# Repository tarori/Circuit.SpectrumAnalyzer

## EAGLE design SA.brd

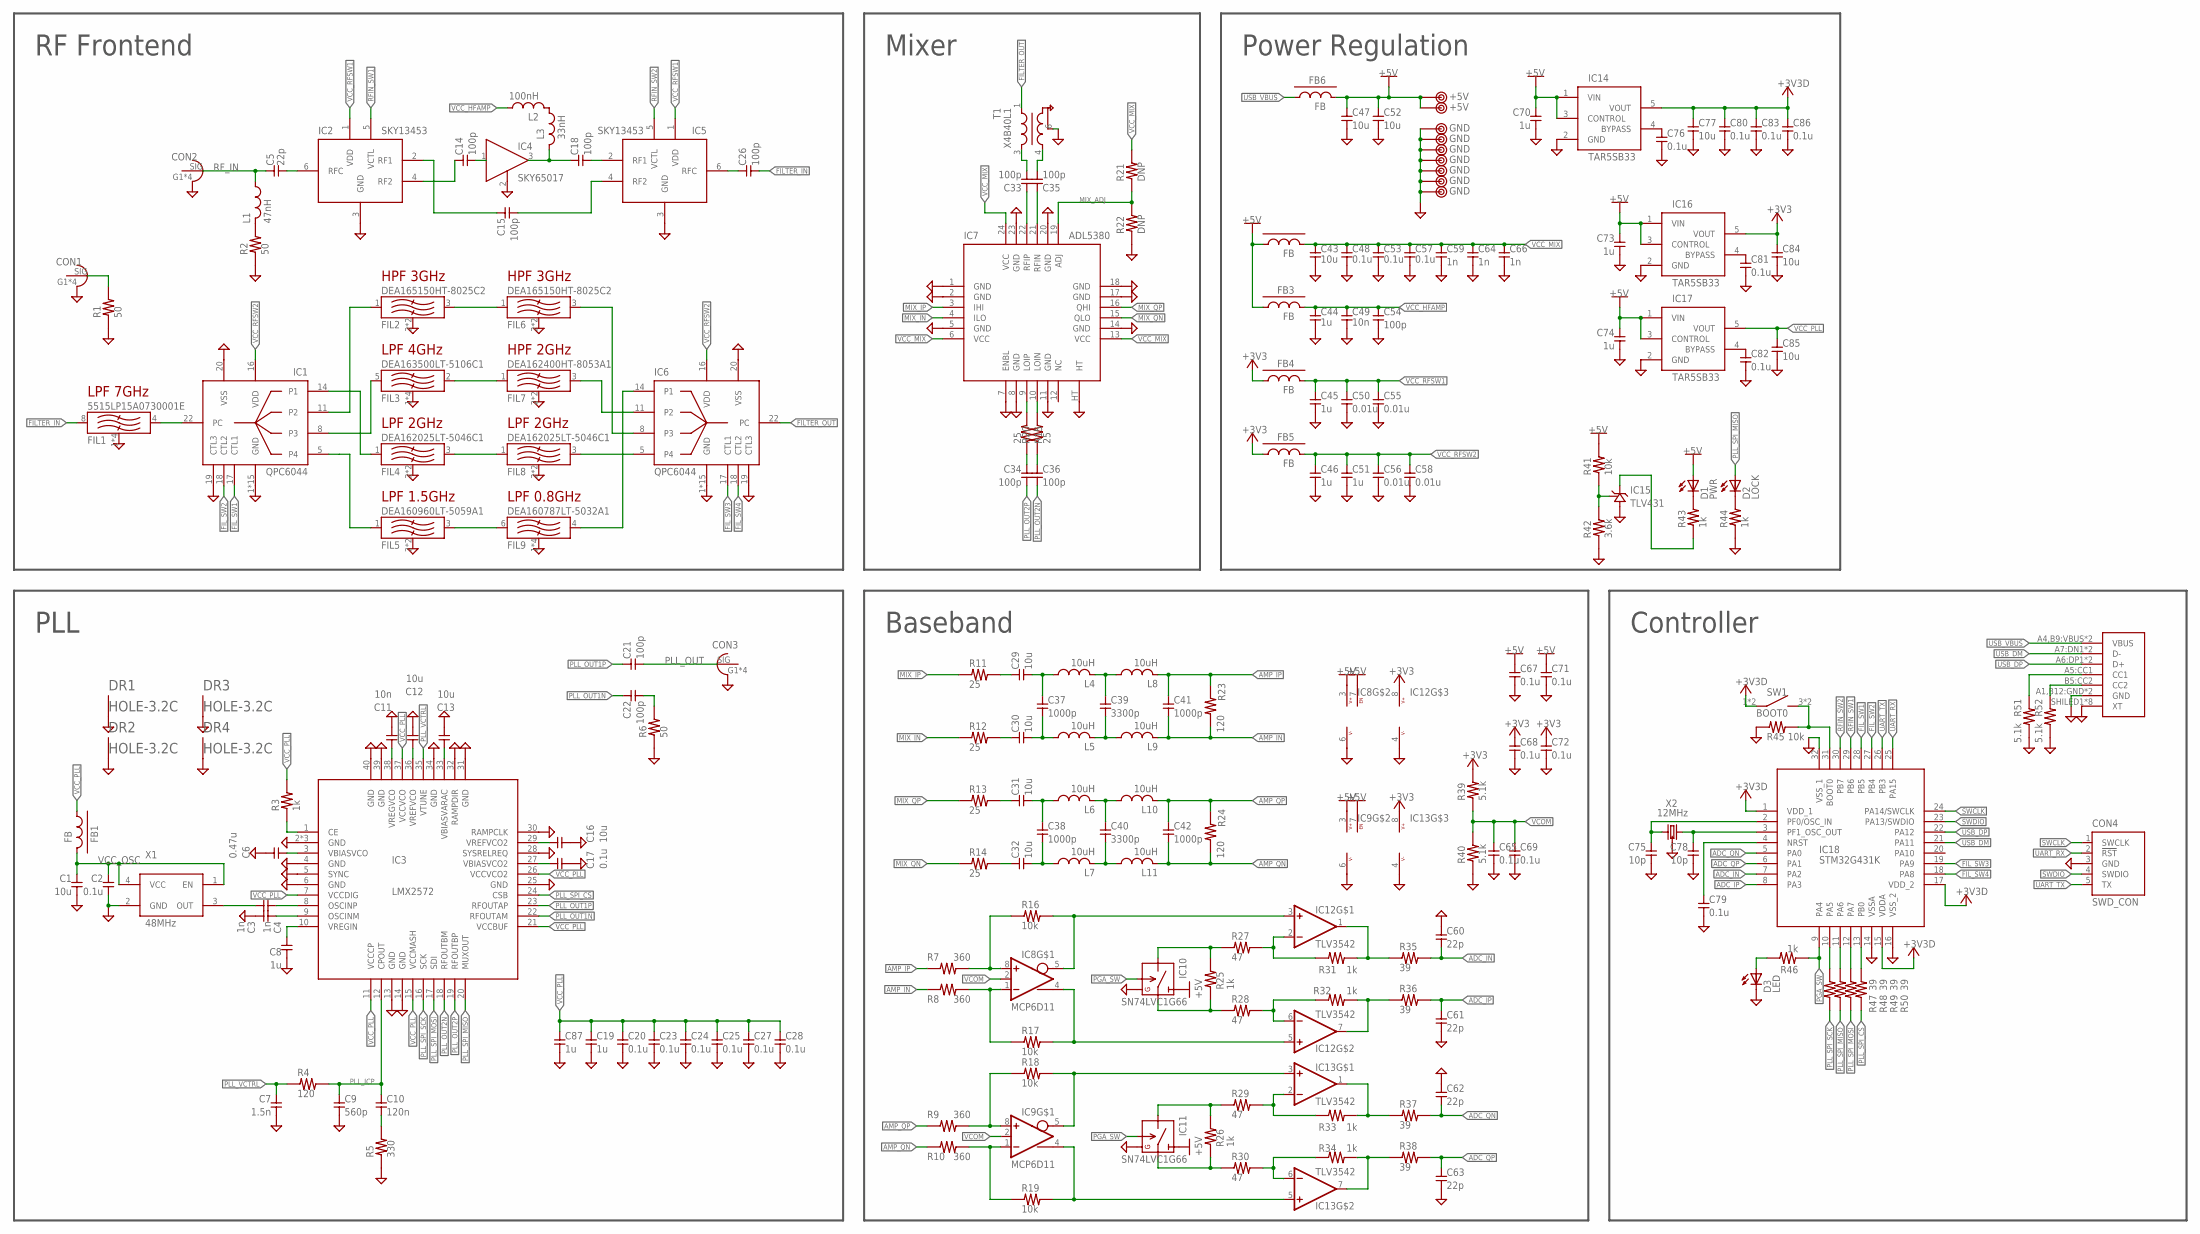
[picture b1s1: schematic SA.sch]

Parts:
C1, C43, C52, C77, C84, C85: 10u; 2012
C2, C17, C20, C23, C24, C25, C27, C28, C48, C53, C57, C65, C67, C68, C69, C71, C72, C76, C79, C80, C81, C82, C83, C86: 0.1u; 1608C
C3, C4, C59, C64, C66: 1n; 1005
C5: 22p; 1005RF
C6: 0.47u; 1608C
C7: 1.5n; 1608C
C8, C19, C44, C45, C46, C51, C70, C73, C74, C87: 1u; 1608C
C9: 560p; 1608C
C10: 120n; 1608C
C11, C49: 10n; 1608C
C12, C13, C16, C29, C30, C31, C32: 10u; 1608C
C14, C15, C18, C21, C22, C26, C33, C34, C35, C36: 100p; 1005RF
C37, C38, C41, C42: 1000p; 1608C
C39, C40: 3300p; 1608C
C47: 10u; 3216
C50, C55, C56, C58: 0.01u; 1608C
C54: 100p; 1005
C60, C61, C62, C63: 22p; 1608C
C75, C78: 10p; 1608C
CON1: DM_L; SMA-EDGE
CON2: RF_IN; SMA-EDGE
CON3: PLL_OUT; SMA-EDGE
CON4: SWD_CON
CON5: USB-C; 5077CR-16-SMC2-BK-TR
D1: PWR; D1608
D2: LOCK; D1608
D3: LED; D1608
DR1, DR2, DR3, DR4: HOLE-3.2C; HOLE_3.2_CON2
FB1, FB2, FB3, FB4, FB5: FB; 1608-FB
FB6: FB; 2012-R
FIL1: 5515LP15A0730001E; RF-FILTER-2012-JOHANSON
FIL2, FIL6: DEA165150HT-8025C2; RF-FILTER-1608-TDK
FIL3: DEA163500LT-5106C1; RF-FILTER-1608-TDK2
FIL4, FIL8: DEA162025LT-5046C1; RF-FILTER-1608-TDK
FIL5: DEA160960LT-5059A1; RF-FILTER-1608-TDK
FIL7: DEA162400HT-8053A1; RF-FILTER-1608-TDK
FIL9: DEA160787LT-5032A1; RF-FILTER-1608-TDK2
IC1, IC6: QPC6044; QFN24-QPC6044
IC2, IC5: SKY13453
IC3: LMX2572; QFN40-LMX
IC4: SKY65017; SOT89-RF
IC7: ADL5380; LFCSP24
IC8, IC9: MCP6D11; MSOP8
IC10, IC11: SN74LVC1G66; SOT23-5-2
IC12, IC13: TLV3542; SOP8-3
IC14, IC16, IC17: TAR5SB33; SOT23-5
IC15: TLV431; SC59
IC18: STM32G431K; TQFP32-08
L1: 47nH; 1005RF
L2: 100nH; 1608-L
L3: 33nH; 1005RF
L4, L5, L6, L7, L8, L9, L10, L11: 10uH; 2012-R
R1, R2, R6: 50; 1005RF
R3, R25, R26, R43, R44, R46: 1k; 1608
R4, R23, R24: 120; 1608
R5: 330; 1608
R7, R8, R9, R10: 360; 1608
R11, R12, R13, R14: 25; 1608
R15, R20: 25; 1005RF
R16, R18, R41, R45: 10k; 1608
R17, R19: 10k; 1608-3
R21, R22: DNP; 1608
R27, R28, R29, R30: 47; 1608-3
R31, R32, R33, R34: 1k; 1608-3
R35, R36, R37, R38, R47, R48, R49, R50: 39; 1608
R39, R40, R51, R52: 5.1k; 1608
R42: 3.6k; 1608
SW1: BOOT0; SKRPACE010
T1: X4B40L1
TP1, TP4: +5V; TESTPIN
TP2, TP3, TP5, TP6, TP7, TP8, TP9: GND; TESTPIN
X1: 48MHz; KC3225
X2: 12MHz; KC3225-CRYSTAL

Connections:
+3V3: C68.1, C72.1, C84.1, FB4.1, FB5.1, IC12.8 (V+), IC13.8 (V+), IC16.5 (VOUT), R39.2
+3V3D: C77.1, C80.1, C83.1, C86.1, IC14.5 (VOUT), IC18.1 (VDD_1), IC18.15 (VDDA), IC18.17 (VDD_2), SW1.1, SW1.2 (1)
+5V: C47.1, C52.1, C67.1, C70.1, C71.1, C73.1, C74.1, D1.A, FB2.1, FB3.1, FB6.2, IC8.3 (V+), IC8.7 (EN), IC9.3 (V+), IC9.7 (EN), IC10.5 (VCC), IC11.5 (VCC), IC14.1 (VIN), IC14.3 (CONTROL), IC16.1 (VIN), IC16.3 (CONTROL), IC17.1 (VIN), IC17.3 (CONTROL), R41.2, TP1.1, TP4.1
ADC_IN: C60.2, IC18.7 (PA2), R35.2
ADC_IP: C61.1, IC18.8 (PA3), R36.2
ADC_QN: C62.2, IC18.5 (PA0), R37.2
ADC_QP: C63.1, IC18.6 (PA1), R38.2
AMP_IN: C41.2, L9.2, R8.1, R23.1
AMP_IP: C41.1, L8.2, R7.1, R23.2
AMP_QN: C42.2, L11.2, R10.1, R24.1
AMP_QP: C42.1, L10.2, R9.1, R24.2
DUMMY_LOAD: CON1.SIG, R1.2
FILTER_IN: C26.2, FIL1.8 (IN)
FILTER_OUT: IC6.22 (PC), T1.1 (IN)
FIL_SW1: IC1.17 (CTL1), IC18.28 (PB5)
FIL_SW2: IC1.18 (CTL2), IC18.27 (PB4)
FIL_SW3: IC6.17 (CTL1), IC18.19 (PA9)
FIL_SW4: IC6.18 (CTL2), IC18.18 (PA8)
GND: C1.2, C2.2, C4.2, C6.2, C7.2, C8.2, C9.2, C11.2, C12.2, C13.2, C16.2, C17.2, C19.2, C20.2, C23.2, C24.2, C25.2, C27.2, C28.2, C43.2, C44.2, C45.2, C46.2, C47.2, C48.2, C49.2, C50.2, C51.2, C52.2, C53.2, C54.2, C55.2, C56.2, C57.2, C58.2, C59.2, C60.1, C61.2, C62.1, C63.2, C64.2, C65.2, C66.2, C67.2, C68.2, C69.2, C70.2, C71.2, C72.2, C73.2, C74.2, C75.2, C76.2, C77.2, C78.2, C79.2, C80.2, C81.2, C82.2, C83.2, C84.2, C85.2, C86.2, C87.2, CON1.G1 (GND), CON1.G2 (GND), CON1.G3 (GND), CON1.G4 (GND), CON2.G1 (GND), CON2.G2 (GND), CON2.G3 (GND), CON2.G4 (GND), CON3.G1 (GND), CON3.G2 (GND), CON3.G3 (GND), CON3.G4 (GND), CON4.3 (GND), CON5.A1,B12:GND (GND), CON5.B1,A12:GND (GND), CON5.SHILED1 (XT), CON5.SHILED2 (XT), CON5.SHILED3 (XT), CON5.SHILED4 (XT), CON5.SHILED5 (XT), CON5.SHILED6 (XT), CON5.SHILED7 (XT), CON5.SHILED8 (XT), D3.K, DR1.T, DR2.T, DR3.T, DR4.T, FIL1.1 (GND), FIL1.3 (GND), FIL1.5 (GND), FIL1.7 (GND), FIL2.2 (GND), FIL2.4 (GND), FIL3.1 (GND), FIL3.3 (GND), FIL3.4 (GND), FIL3.6 (GND), FIL4.2 (GND), FIL4.4 (GND), FIL5.2 (GND), FIL5.4 (GND), FIL6.2 (GND), FIL6.4 (GND), FIL7.2 (GND), FIL7.4 (GND), FIL8.2 (GND), FIL8.4 (GND), FIL9.1 (GND), FIL9.2 (GND), FIL9.3 (GND), FIL9.5 (GND), IC1.1 (GND), IC1.2 (GND), IC1.3 (GND), IC1.4 (GND), IC1.6 (GND), IC1.7 (GND), IC1.9 (GND), IC1.10 (GND), IC1.12 (GND), IC1.13 (GND), IC1.15 (GND), IC1.19 (CTL3), IC1.20 (VSS), IC1.21 (GND), IC1.23 (GND), IC1.24 (GND), IC1.HT (GND), IC2.3 (GND), IC3.2 (GND), IC3.4 (GND), IC3.5 (SYNC), IC3.6 (GND), IC3.13 (GND), IC3.14 (GND), IC3.25 (GND), IC3.28 (SYSRELREQ), IC3.30 (RAMPCLK), IC3.31 (GND), IC3.32 (RAMPDIR), IC3.34 (GND), IC3.39 (GND), IC3.40 (GND), IC3.HT (GND), IC3.HT2 (GND), IC4.2 (GND), IC5.3 (GND), IC6.1 (GND), IC6.2 (GND), IC6.3 (GND), IC6.4 (GND), IC6.6 (GND), IC6.7 (GND), IC6.9 (GND), IC6.10 (GND), IC6.12 (GND), IC6.13 (GND), IC6.15 (GND), IC6.19 (CTL3), IC6.20 (VSS), IC6.21 (GND), IC6.23 (GND), IC6.24 (GND), IC6.HT (GND), IC7.1 (GND), IC7.2 (GND), IC7.5 (GND), IC7.7 (ENBL), IC7.8 (GND), IC7.11 (GND), IC7.14 (GND), IC7.17 (GND), IC7.18 (GND), IC7.20 (GND), IC7.23 (GND), IC7.HT, IC8.6 (V-), IC9.6 (V-), IC10.3 (GND), IC11.3 (GND), IC12.4 (V-), IC13.4 (V-), IC14.2 (GND), IC15.3 (GND), IC16.2 (GND), IC17.2 (GND), IC18.14 (VSSA), IC18.16 (VSS_2), IC18.32 (VSS_1), R1.1, R2.1, R5.1, R6.1, R22.1, R40.1, R42.1, R44.1, R45.1, R51.1, R52.1, T1.6 (GND), TP2.1, TP3.1, TP5.1, TP6.1, TP7.1, TP8.1, TP9.1, X1.2 (GND), X2.2 (GND), X2.4 (GND)
MIX_ADJ: IC7.19 (ADJ), R21.1, R22.2
MIX_IN: IC7.4 (ILO), R12.1
MIX_IP: IC7.3 (IHI), R11.1
MIX_QN: IC7.15 (QLO), R14.1
MIX_QP: IC7.16 (QHI), R13.1
unnamed: C14.1, IC2.4 (RF2)
unnamed: C10.2, R5.2
unnamed: C39.1, L4.2, L8.1
unnamed: C35.2, T1.4 (OUTN)
unnamed: C13.1, IC3.33 (VBIASVARAC)
unnamed: C39.2, L5.2, L9.1
unnamed: C31.2, C38.1, L6.1
unnamed: C33.1, IC7.22 (RFIP)
unnamed: C32.2, C38.2, L7.1
unnamed: C40.1, L6.2, L10.1
unnamed: C40.2, L7.2, L11.1
unnamed: C16.1, IC3.29 (VREFVCO2)
unnamed: C82.1, IC17.4 (BYPASS)
unnamed: L2.2, L3.1
unnamed: IC15.1 (REF), R41.1, R42.2
unnamed: IC15.2 (OUT), R43.1
unnamed: C34.1, R15.1
unnamed: C36.1, R20.1
unnamed: IC18.10 (PA5), R47.1
unnamed: C35.1, IC7.21 (RFIN)
unnamed: C3.2, X1.3 (OUT)
unnamed: C81.1, IC16.4 (BYPASS)
unnamed: L1.2, R2.2
unnamed: IC18.11 (PA6), R48.1
unnamed: IC18.12 (PA7), R49.1
unnamed: C22.2, R6.2
unnamed: IC18.13 (PB0), R50.1
unnamed: D3.A, R46.2
unnamed: CON5.B5:CC2 (CC2), R52.2
unnamed: CON5.A5:CC1 (CC1), R51.2
unnamed: C29.2, C37.1, L4.1
unnamed: C30.2, C37.2, L5.1
unnamed: IC7.9 (LOIP), R15.2
unnamed: IC7.10 (LOIN), R20.2
unnamed: D1.K, R43.2
unnamed: D2.K, R44.2
unnamed: FIL1.4 (OUT), IC1.22 (PC)
unnamed: C15.1, IC2.2 (RF1)
unnamed: C15.2, IC5.4 (RF2)
unnamed: C26.1, IC5.6 (RFC)
unnamed: C5.2, IC2.6 (RFC)
unnamed: C14.2, IC4.1 (IN)
unnamed: C18.1, IC4.3 (OUT), L3.2
unnamed: FIL5.1 (IN), IC1.5 (P4)
unnamed: FIL4.1 (IN), IC1.14 (P1)
unnamed: FIL2.1 (IN), IC1.11 (P2)
unnamed: FIL4.3 (OUT), FIL8.1 (IN)
unnamed: FIL6.3 (OUT), IC6.8 (P3)
unnamed: FIL5.3 (OUT), FIL9.6 (IN)
unnamed: FIL3.2 (OUT), FIL7.1 (IN)
unnamed: FIL7.3 (OUT), IC6.11 (P2)
unnamed: FIL9.4 (OUT), IC6.14 (P1)
unnamed: FIL8.3 (OUT), IC6.5 (P4)
unnamed: C4.1, IC3.9 (OSCINM)
unnamed: C33.2, T1.3 (OUTP)
unnamed: C18.2, IC5.2 (RF1)
unnamed: C29.1, R11.2
unnamed: C30.1, R12.2
unnamed: C31.1, R13.2
unnamed: C32.1, R14.2
unnamed: IC8.8 (+IN), R7.2, R16.1
unnamed: IC8.1 (-IN), R8.2, R17.1
unnamed: IC8.5 (-OUT), IC12.3 (+IN), R16.2
unnamed: IC13.2 (-IN), R29.2, R33.2
unnamed: IC9.8 (+IN), R9.2, R18.1
unnamed: IC9.1 (-IN), R10.2, R19.1
unnamed: IC12.6 (-IN), R28.2, R32.2
unnamed: IC9.5 (-OUT), IC13.3 (+IN), R18.2
unnamed: C76.1, IC14.4 (BYPASS)
unnamed: C75.1, IC18.2 (PF0/OSC_IN), X2.3 (2)
unnamed: C78.1, IC18.3 (PF1_OSC_OUT), X2.1
unnamed: FIL2.3 (OUT), FIL6.1 (IN)
unnamed: IC12.2 (-IN), R27.2, R31.2
unnamed: IC8.4 (+OUT), IC12.5 (+IN), R17.2
unnamed: IC12.1 (OUT), R31.1, R35.1
unnamed: IC9.4 (+OUT), IC13.5 (+IN), R19.2
unnamed: IC13.7 (OUT), R34.1, R38.1
unnamed: IC12.7 (OUT), R32.1, R36.1
unnamed: IC13.6 (-IN), R30.2, R34.2
unnamed: IC13.1 (OUT), R33.1, R37.1
unnamed: IC10.2 (B), R25.1, R28.1
unnamed: IC10.1 (A), R25.2, R27.1
unnamed: IC11.2 (B), R26.1, R30.1
unnamed: IC11.1 (A), R26.2, R29.1
unnamed: FIL3.5 (IN), IC1.8 (P3)
unnamed: C3.1, IC3.8 (OSCINP)
unnamed: C12.1, IC3.36 (VREFVCO)
unnamed: C11.1, IC3.38 (VREGVCO)
unnamed: C6.1, IC3.3 (VBIASVCO)
unnamed: C8.1, IC3.10 (VREGIN)
unnamed: C17.1, IC3.27 (VBIASVCO2)
PGA_SW: IC10.4 (S), IC11.4 (S), IC18.9 (PA4), R46.1
PLL_EN: IC3.1 (CE), R3.1
PLL_ICP: C9.1, C10.1, IC3.12 (CPOUT), R4.2
PLL_OUT: C21.2, CON3.SIG
PLL_OUT1N: C22.1, IC3.22 (RFOUTAM)
PLL_OUT1P: C21.1, IC3.23 (RFOUTAP)
PLL_OUT2N: C36.2, IC3.18 (RFOUTBM)
PLL_OUT2P: C34.2, IC3.19 (RFOUTBP)
PLL_SPI_CS: IC3.24 (CSB), R50.2
PLL_SPI_MISO: D2.A, IC3.20 (MUXOUT), R48.2
PLL_SPI_MOSI: IC3.17 (SDI), R49.2
PLL_SPI_SCK: IC3.16 (SCK), R47.2
PLL_VCTRL: C7.1, IC3.35 (VTUNE), R4.1
RFIN_SW1: IC2.5 (VCTL), IC18.29 (PB6)
RFIN_SW2: IC5.5 (VCTL), IC18.30 (PB7)
RF_IN: C5.1, CON2.SIG, L1.1
ST_BOOT0: IC18.31 (BOOT0), R45.2, SW1.3 (2), SW1.4 (2)
ST_NRST: C79.1, IC18.4 (NRST)
SWCLK: CON4.1 (SWCLK), IC18.24 (PA14/SWCLK)
SWDIO: CON4.4 (SWDIO), IC18.23 (PA13/SWDIO)
UART_RX: CON4.2 (!RST), IC18.25 (PA15)
UART_TX: CON4.5 (TX), IC18.26 (PB3)
USB_DM: CON5.A7:DN1 (D-), CON5.B7:DN2 (D-), IC18.21 (PA11)
USB_DP: CON5.A6:DP1 (D+), CON5.B6:DP2 (D+), IC18.22 (PA12)
USB_VBUS: CON5.A4,B9:VBUS (VBUS), CON5.B4,A9:VBUS (VBUS), FB6.1
VCC_HFAMP: C44.1, C49.1, C54.1, FB3.2, L2.1
VCC_MIX: C43.1, C48.1, C53.1, C57.1, C59.1, C64.1, C66.1, FB2.2, IC7.6 (VCC), IC7.13 (VCC), IC7.24 (VCC), R21.2
VCC_OSC: C1.1, C2.1, FB1.2, X1.1 (EN), X1.4 (VCC)
VCC_PLL: C19.1, C20.1, C23.1, C24.1, C25.1, C27.1, C28.1, C85.1, C87.1, FB1.1, IC3.7 (VCCDIG), IC3.11 (VCCCP), IC3.15 (VCCMASH), IC3.21 (VCCBUF), IC3.26 (VCCVCO2), IC3.37 (VCCVCO), IC17.5 (VOUT), R3.2
VCC_RFSW1: C45.1, C50.1, C55.1, FB4.2, IC2.1 (VDD), IC5.1 (VDD)
VCC_RFSW2: C46.1, C51.1, C56.1, C58.1, FB5.2, IC1.16 (VDD), IC6.16 (VDD)
VCOM: C65.1, C69.1, IC8.2 (CM), IC9.2 (CM), R39.1, R40.2

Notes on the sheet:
LPF 7GHz
HPF 3GHz
LPF 4GHz
LPF 2GHz
LPF 1.5GHz
LPF 0.8GHz
HPF 2GHz
RF Frontend
Mixer
PLL
Baseband
Power Regulation
Controller

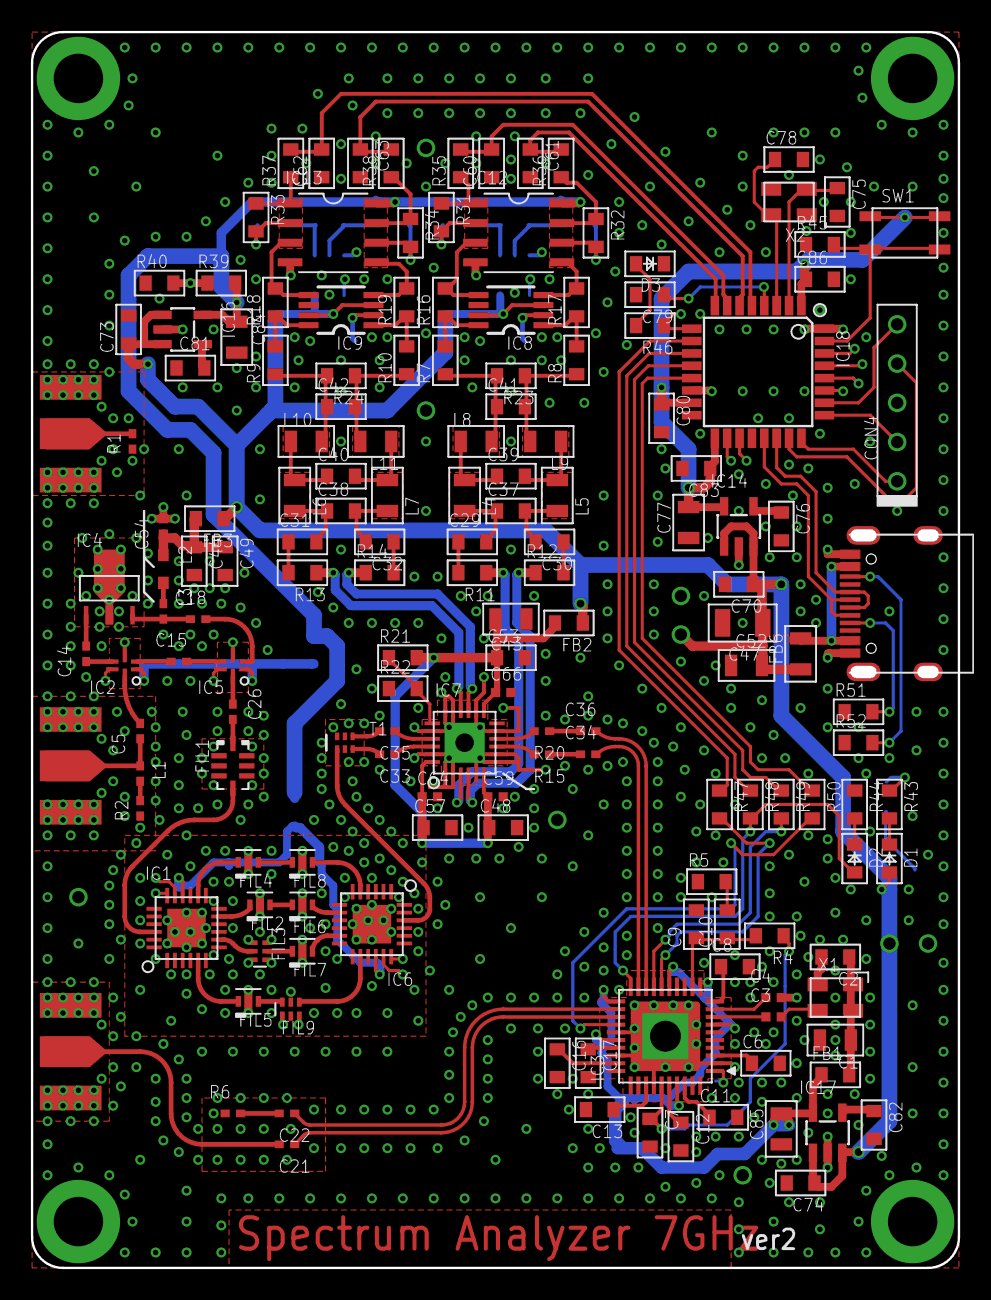
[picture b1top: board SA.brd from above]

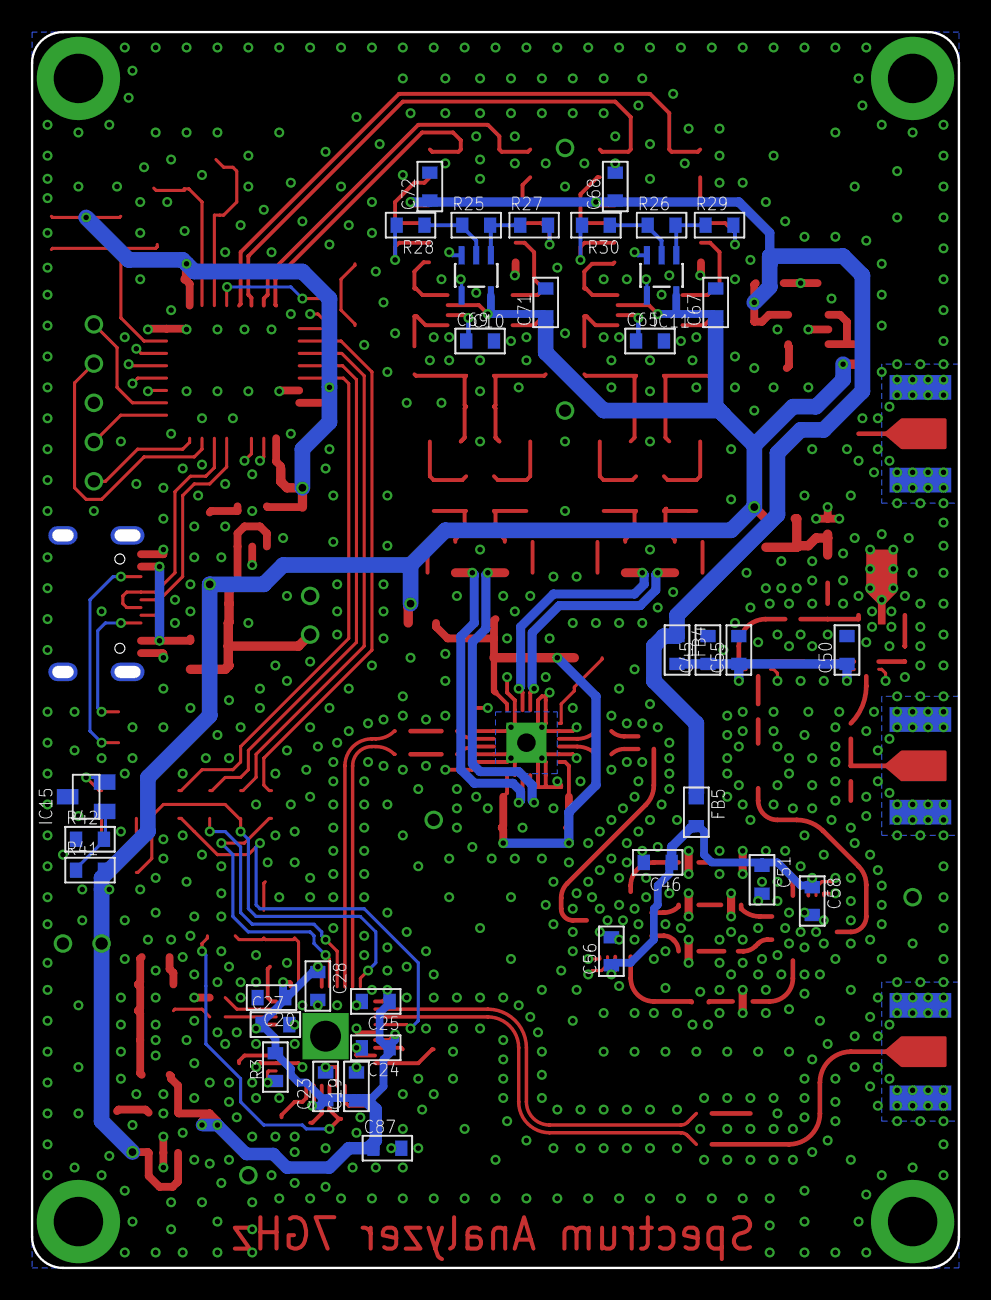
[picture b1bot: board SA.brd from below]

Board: 4 copper layers, 60.0 x 80.0 mm, 208 parts (35 on the bottom side), 147 nets.

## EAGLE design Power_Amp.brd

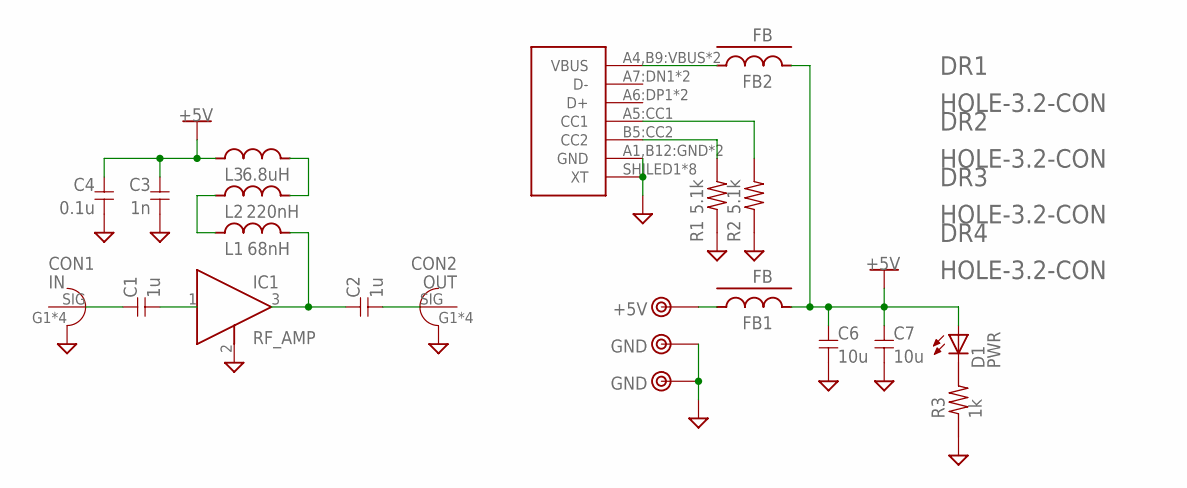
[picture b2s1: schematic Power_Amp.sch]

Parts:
C1, C2: 1u; 1608-3
C3: 1n; 1005
C4: 0.1u; 1608C
C6, C7: 10u; 2012
CON1: IN; SMA-EDGE3
CON2: OUT; SMA-EDGE3
CON3: USB-C; 5077CR-16-SMC2-BK-TR
D1: PWR; D1608
DR1, DR2, DR3, DR4: HOLE-3.2-CON; HOLE_3.2_CON
FB1, FB2: FB; 1608-FB
IC1: RF_AMP; SOT89
L1: 68nH; 1005
L2: 220nH; 1608
L3: 6.8uH; 1608
R1, R2: 5.1k; 1608
R3: 1k; 1608
TP1: +5V; TESTPIN
TP2, TP3: GND; TESTPIN

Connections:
+5V: C3.1, C4.1, C6.1, C7.1, D1.A, FB1.2, FB2.2, L3.1
GND: C3.2, C4.2, C6.2, C7.2, CON1.G1 (GND), CON1.G2 (GND), CON1.G3 (GND), CON1.G4 (GND), CON2.G1 (GND), CON2.G2 (GND), CON2.G3 (GND), CON2.G4 (GND), CON3.A1,B12:GND (GND), CON3.B1,A12:GND (GND), CON3.SHILED1 (XT), CON3.SHILED2 (XT), CON3.SHILED3 (XT), CON3.SHILED4 (XT), CON3.SHILED5 (XT), CON3.SHILED6 (XT), CON3.SHILED7 (XT), CON3.SHILED8 (XT), IC1.2 (GND), R1.1, R2.1, R3.1, TP2.1, TP3.1
unnamed: C1.2, IC1.1 (IN)
unnamed: C1.1, CON1.SIG
unnamed: C2.1, IC1.3 (OUT), L1.2
unnamed: L1.1, L2.1
unnamed: L2.2, L3.2
unnamed: C2.2, CON2.SIG
unnamed: FB1.1, TP1.1
unnamed: D1.K, R3.2
unnamed: CON3.B5:CC2 (CC2), R1.2
unnamed: CON3.A5:CC1 (CC1), R2.2
unnamed: CON3.A4,B9:VBUS (VBUS), CON3.B4,A9:VBUS (VBUS), FB2.1

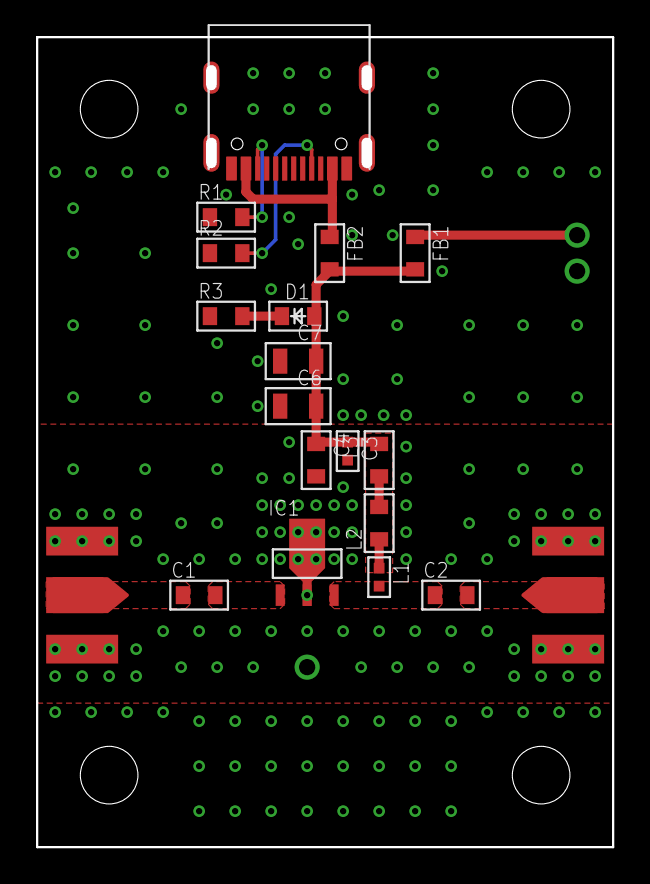
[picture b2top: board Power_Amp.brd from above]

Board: 2 copper layers, 32.0 x 45.0 mm, 26 parts (0 on the bottom side), 13 nets.

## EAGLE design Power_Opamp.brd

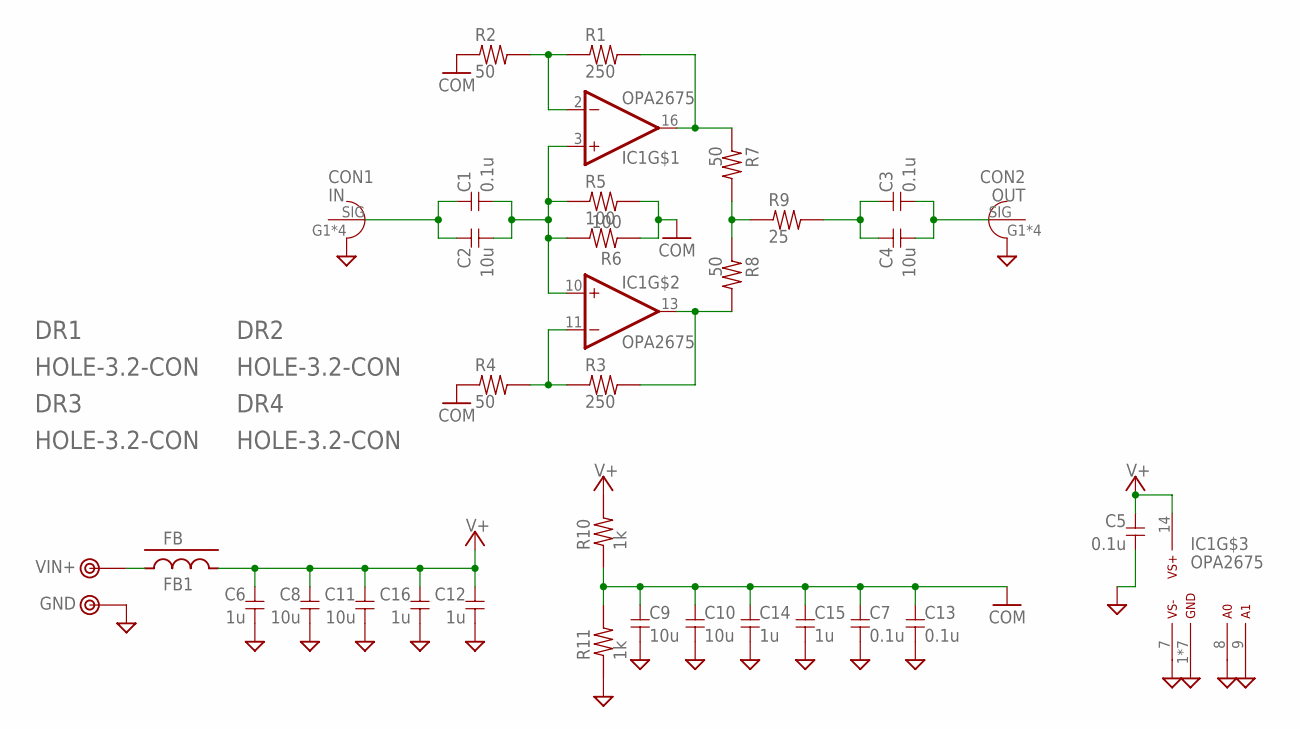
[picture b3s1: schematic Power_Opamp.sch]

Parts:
C1, C3: 0.1u; 1608C
C2, C4, C10, C11: 10u; 2012
C5, C7, C13: 0.1u; 1005
C6, C12, C14, C15, C16: 1u; 1608C
C8, C9: 10u; 3216
CON1: IN; SMA-EDGE
CON2: OUT; SMA-EDGE
DR1, DR2, DR3, DR4: HOLE-3.2-CON; HOLE_3.2_CON
FB1: FB; 2012-J
IC1: OPA2675; VQFN16
R1, R3: 250; 1608-3
R2, R4: 50; 1608-3
R5, R6: 100; 1608-3
R7, R8: 50; 1608
R9: 25; 1608
R10, R11: 1k; 1608
TP1: VIN+; TESTPIN-BIG
TP2: GND; TESTPIN-BIG

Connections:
AMP_IN: C1.2, C2.2, IC1.3 (+IN), IC1.10 (+IN), R5.1, R6.2
AMP_OUT: C3.1, C4.1, R9.2
COM: C7.1, C9.1, C10.1, C13.1, C14.1, C15.1, R2.1, R4.1, R5.2, R6.1, R10.1, R11.2
GND: C5.2, C6.2, C7.2, C8.2, C9.2, C10.2, C11.2, C12.2, C13.2, C14.2, C15.2, C16.2, CON1.G1 (GND), CON1.G2 (GND), CON1.G3 (GND), CON1.G4 (GND), CON2.G1 (GND), CON2.G2 (GND), CON2.G3 (GND), CON2.G4 (GND), IC1.1 (GND), IC1.4 (GND), IC1.5 (GND), IC1.6 (GND), IC1.7 (VS-), IC1.8 (A0), IC1.9 (A1), IC1.12 (GND), IC1.15 (GND), IC1.HT (GND), R11.1, TP2.1
unnamed: IC1.11 (-IN), R3.1, R4.2
unnamed: IC1.2 (-IN), R1.1, R2.2
unnamed: IC1.13 (OUT), R3.2, R8.2
unnamed: IC1.16 (OUT), R1.2, R7.1
unnamed: C1.1, C2.1, CON1.SIG
unnamed: C3.2, C4.2, CON2.SIG
unnamed: R7.2, R8.1, R9.1
unnamed: FB1.2, TP1.1
V+: C5.1, C6.1, C8.1, C11.1, C12.1, C16.1, FB1.1, IC1.14 (VS+), R10.2

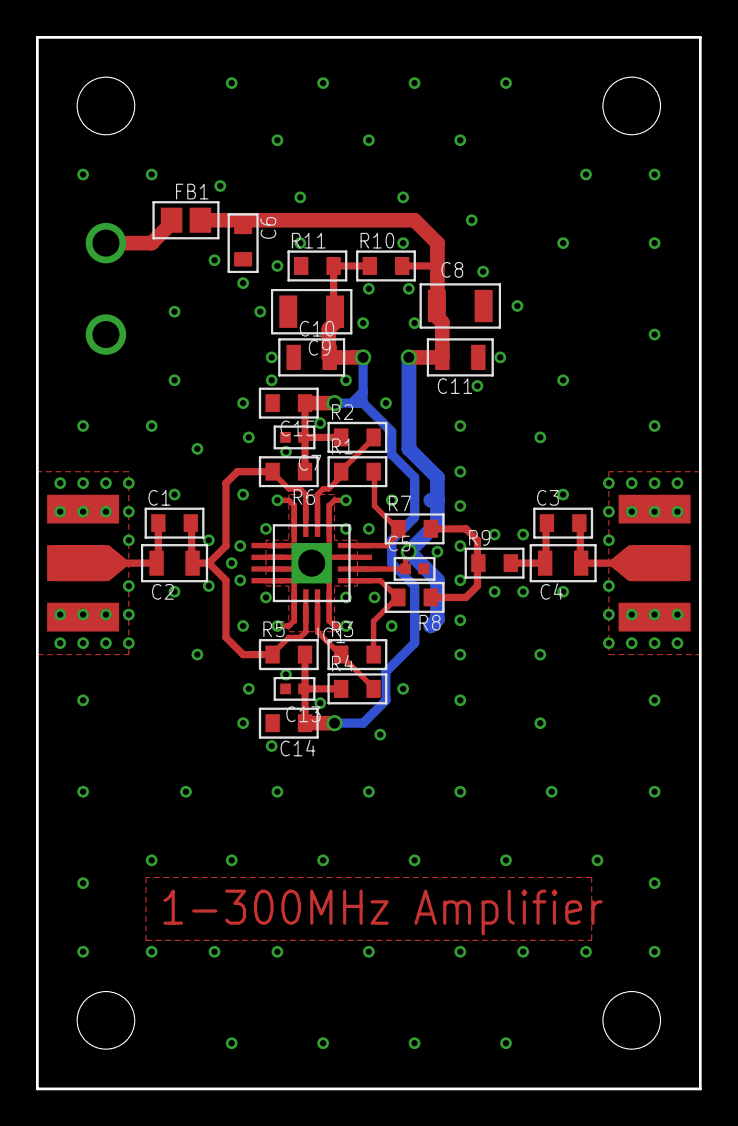
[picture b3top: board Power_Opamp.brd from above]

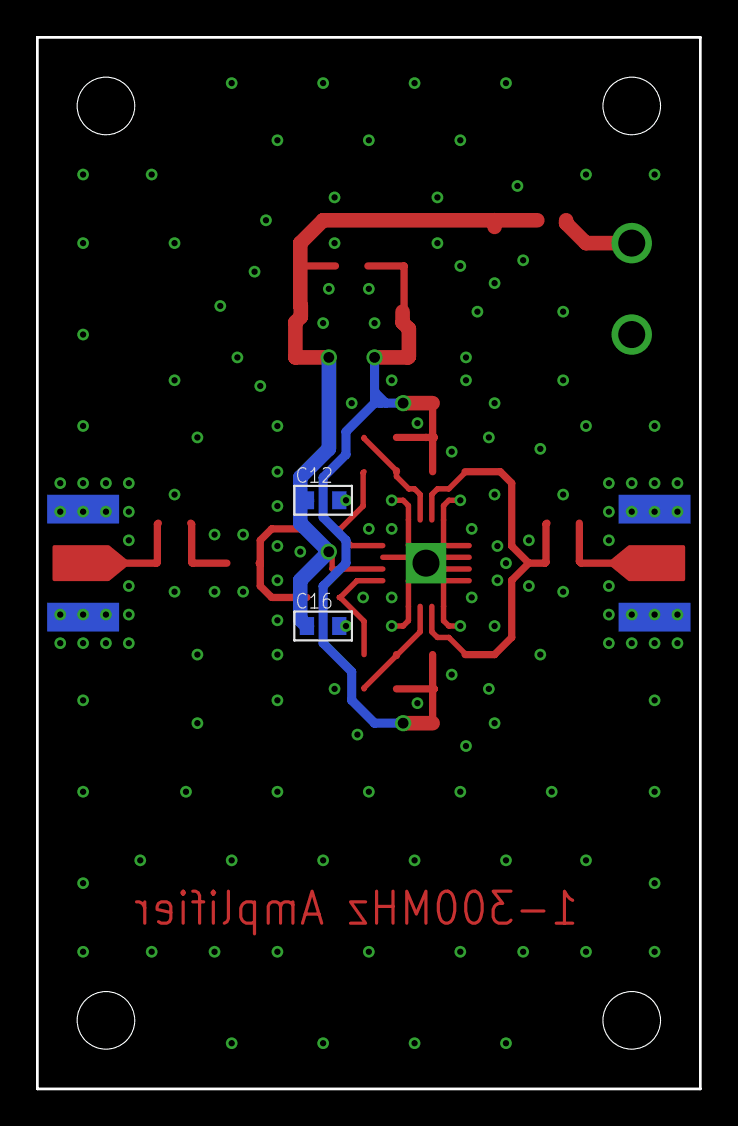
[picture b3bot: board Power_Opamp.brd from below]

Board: 2 copper layers, 36.8 x 58.4 mm, 37 parts (2 on the bottom side), 13 nets.

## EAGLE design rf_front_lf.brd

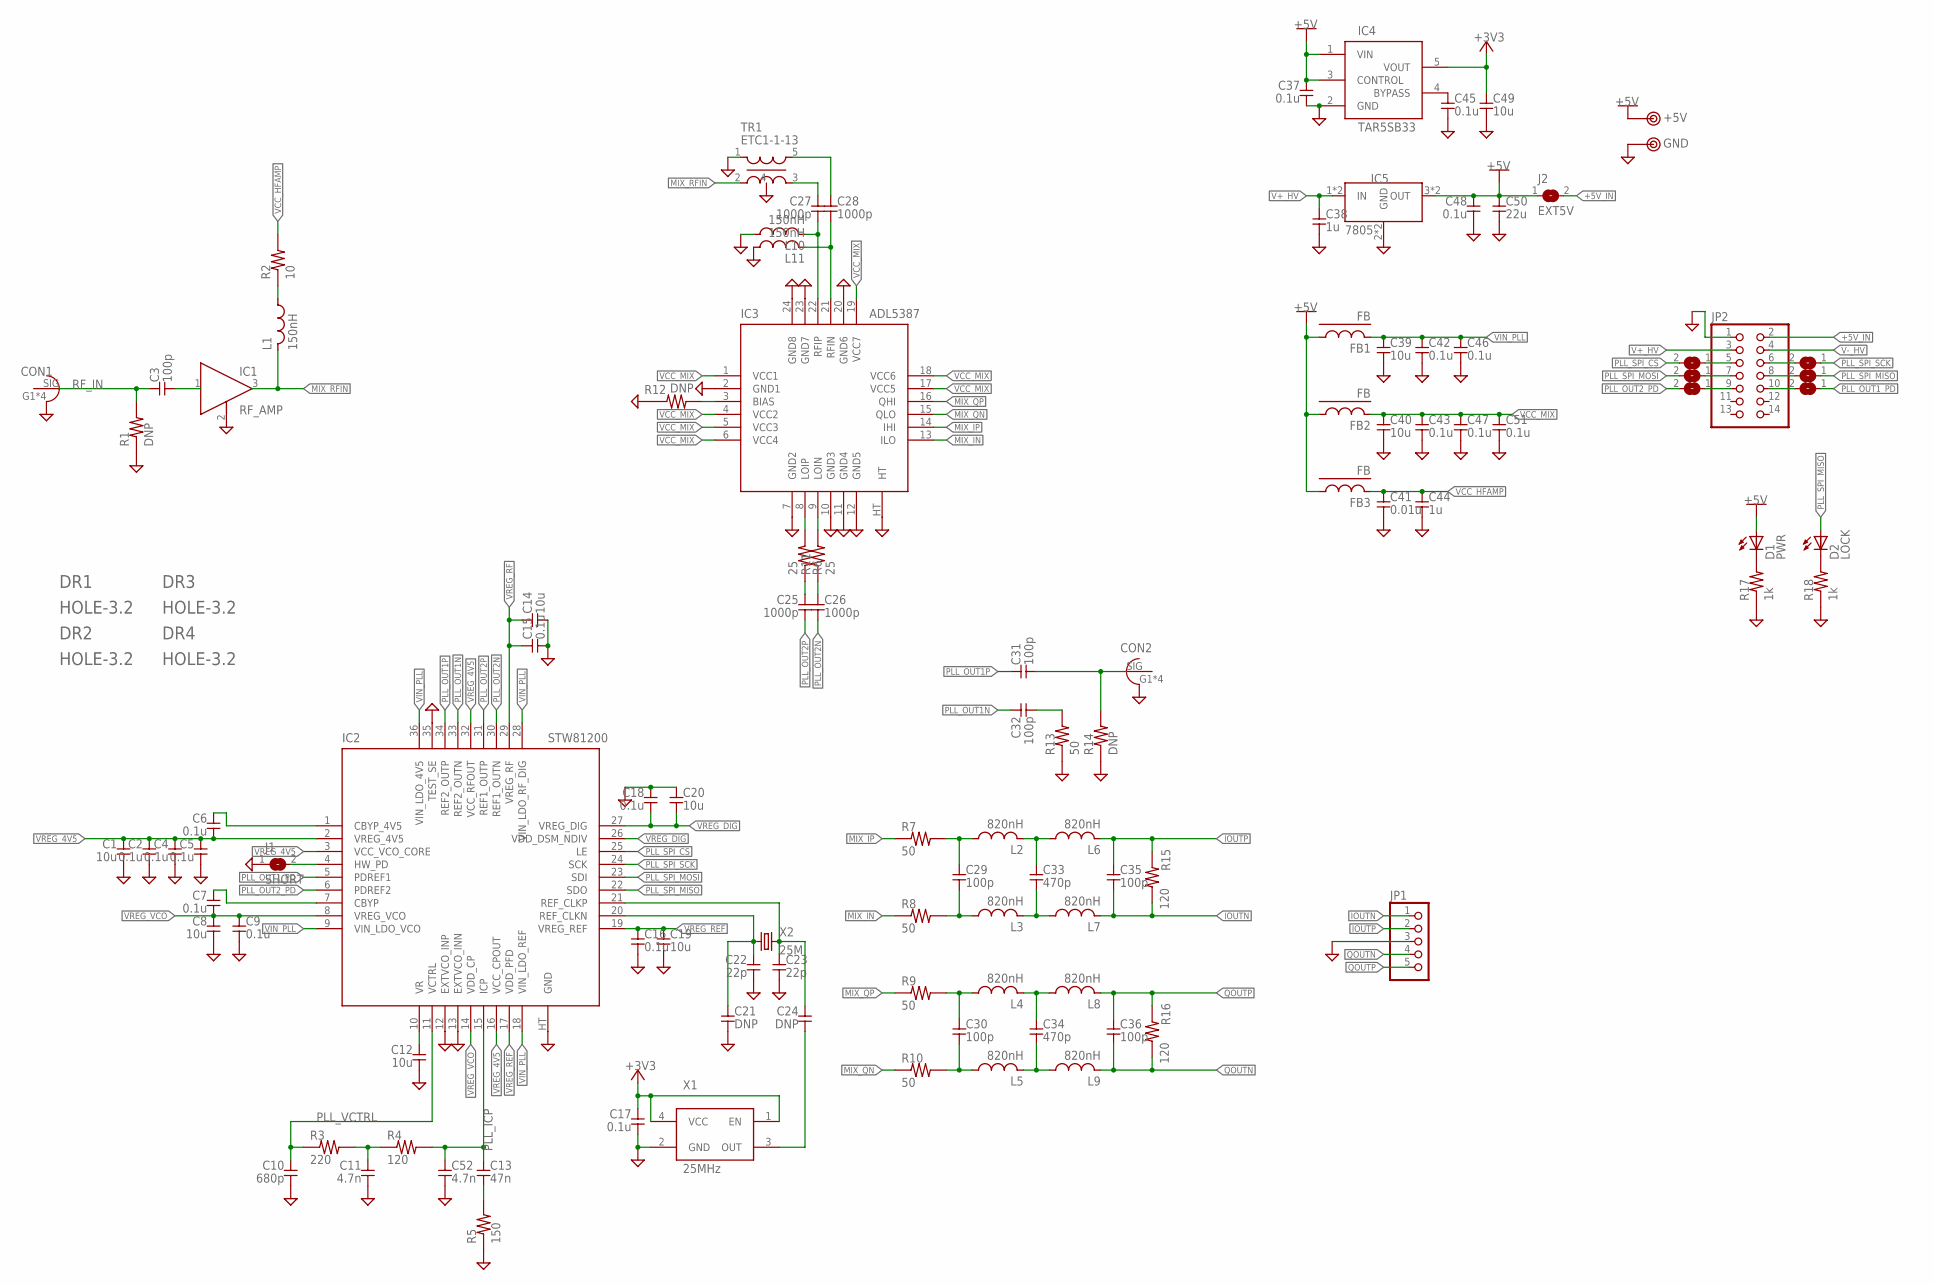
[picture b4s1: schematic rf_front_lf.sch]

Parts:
C1, C8, C12, C14, C19, C20, C49: 10u; 1608
C2, C4, C5, C6, C7, C9, C15, C16, C17, C18, C37, C42, C43, C45, C46, C47, C48, C51: 0.1u; 1608
C3, C29, C30, C31, C32, C35, C36: 100p; 1608
C10: 680p; 1608
C11, C52: 4.7n; 1608
C13: 47n; 1608
C21, C24: DNP; 1608
C22, C23: 22p; 1608
C25, C26, C27, C28: 1000p; 1608
C33, C34: 470p; 1608
C38, C44: 1u; 1608
C39, C40: 10u; 2012
C41: 0.01u; 1608
C50: 22u; 3225
CON1: RF_IN; SMA-EDGE
CON2: PLL_OUT; SMA-EDGE
D1: PWR; D1608
D2: LOCK; D1608
DR1, DR2, DR3, DR4: HOLE-3.2; HOLE_3.2
FB1, FB2, FB3: FB; 1608-J
IC1: RF_AMP; SOT89
IC2: STW81200; VFQFPN36
IC3: ADL5387; LFCSP24
IC4: TAR5SB33; SOT23-5
IC5: 7805; TO220-SOP-DUAL
J1: SHORT; 1608-J
J2: EXT5V; 1608-J
J3: CS; 1608-J
J4: MOSI; 1608-J
J5: PD2; 1608-J
J6: SCK; 1608-J
J7: MISO; 1608-J
J8: PD1; 1608-J
JP1: PINHD-1X5; 1X05
JP2: PINHD-2X7; 2X07
L1, L10, L11: 150nH; 1608
L2, L3, L4, L5, L6, L7, L8, L9: 820nH; 1608
R1, R12, R14: DNP; 1608
R2: 10; 1608
R3: 220; 1608
R4, R15, R16: 120; 1608
R5: 150; 1608
R6, R11: 25; 1608
R7, R8, R9, R10, R13: 50; 1608
R17, R18: 1k; 1608
TP1: +5V; TESTPIN
TP2: GND; TESTPIN
TR1: ETC1-1-13
X1: 25MHz; KC3225
X2: 25M; HC49/S

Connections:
+3V3: C17.1, C49.1, IC4.5 (VOUT), X1.1 (EN), X1.4 (VCC)
+5V: C37.1, C48.1, C50.1, D1.A, FB1.1, FB2.1, FB3.1, IC4.1 (VIN), IC4.3 (CONTROL), IC5.3 (OUT), IC5.6 (OUT), J2.1, TP1.1
+5V_IN: J2.2, JP2.2
GND: C1.2, C2.2, C4.2, C5.2, C8.2, C9.2, C10.2, C11.2, C12.2, C14.2, C15.2, C16.2, C17.2, C18.1, C19.2, C20.1, C21.2, C22.2, C23.2, C37.2, C38.2, C39.2, C40.2, C41.2, C42.2, C43.2, C44.2, C45.2, C46.2, C47.2, C48.2, C49.2, C50.2, C51.2, C52.2, CON1.G1 (GND), CON1.G2 (GND), CON1.G3 (GND), CON1.G4 (GND), CON2.G1 (GND), CON2.G2 (GND), CON2.G3 (GND), CON2.G4 (GND), IC1.2 (GND), IC2.12 (EXTVCO_INP), IC2.13 (EXTVCO_INN), IC2.35 (TEST_SE), IC2.HT (GND), IC3.2 (GND1), IC3.7 (GND2), IC3.10 (GND3), IC3.11 (GND4), IC3.12 (GND5), IC3.20 (GND6), IC3.23 (GND7), IC3.24 (GND8), IC3.HT, IC4.2 (GND), IC5.2 (GND), IC5.5 (GND), J1.1, JP1.3, JP2.1, L10.1, L11.1, R1.1, R5.1, R12.1, R13.1, R14.1, R17.1, R18.1, TP2.1, TR1.1, TR1.4, X1.2 (GND)
IOUTN: C35.2, JP1.1, L7.2, R15.1
IOUTP: C35.1, JP1.2, L6.2, R15.2
MIX_IN: IC3.13 (ILO), R8.1
MIX_IP: IC3.14 (IHI), R7.1
MIX_QN: IC3.15 (QLO), R10.1
MIX_QP: IC3.16 (QHI), R9.1
MIX_RFIN: IC1.3 (OUT), L1.2, TR1.2
unnamed: C3.2, IC1.1 (IN)
unnamed: C13.2, R5.2
unnamed: C33.1, L2.2, L6.1
unnamed: C27.2, IC3.22 (RFIP), L10.2
unnamed: C11.1, R3.2, R4.1
unnamed: C33.2, L3.2, L7.1
unnamed: C30.1, L4.1, R9.2
unnamed: C28.2, IC3.21 (RFIN), L11.2
unnamed: C30.2, L5.1, R10.2
unnamed: C34.1, L4.2, L8.1
unnamed: C34.2, L5.2, L9.1
unnamed: C12.1, IC2.10 (VR)
unnamed: C6.1, IC2.1 (CBYP_4V5)
unnamed: C21.1, C22.1, IC2.20 (REF_CLKN), X2.1
unnamed: C7.1, IC2.7 (CBYP)
unnamed: C23.1, C24.1, IC2.21 (REF_CLKP), X2.2
unnamed: C27.1, TR1.3
unnamed: C28.1, TR1.5
unnamed: L1.1, R2.1
unnamed: IC3.9 (LOIN), R11.2
unnamed: C24.2, X1.3 (OUT)
unnamed: C45.1, IC4.4 (BYPASS)
unnamed: C31.2, CON2.SIG, R14.2
unnamed: J3.1, JP2.5
unnamed: J4.1, JP2.7
unnamed: C32.2, R13.2
unnamed: J5.1, JP2.9
unnamed: J8.2, JP2.10
unnamed: J7.2, JP2.8
unnamed: J6.2, JP2.6
unnamed: IC2.4 (HW_PD), J1.2
unnamed: C29.1, L2.1, R7.2
unnamed: C29.2, L3.1, R8.2
unnamed: D1.K, R17.2
unnamed: IC3.3 (BIAS), R12.2
unnamed: IC3.8 (LOIP), R6.2
unnamed: C25.1, R6.1
unnamed: C26.1, R11.1
unnamed: D2.K, R18.2
PLL_ICP: C13.1, C52.1, IC2.15 (ICP), R4.2
PLL_OUT1N: C32.1, IC2.33 (REF2_OUTN)
PLL_OUT1P: C31.1, IC2.34 (REF2_OUTP)
PLL_OUT1_PD: IC2.5 (PDREF1), J8.1
PLL_OUT2N: C26.2, IC2.30 (REF1_OUTN)
PLL_OUT2P: C25.2, IC2.31 (REF1_OUTP)
PLL_OUT2_PD: IC2.6 (PDREF2), J5.2
PLL_SPI_CS: IC2.25 (LE), J3.2
PLL_SPI_MISO: D2.A, IC2.22 (SDO), J7.1
PLL_SPI_MOSI: IC2.23 (SDI), J4.2
PLL_SPI_SCK: IC2.24 (SCK), J6.1
PLL_VCTRL: C10.1, IC2.11 (VCTRL), R3.1
QOUTN: C36.2, JP1.4, L9.2, R16.1
QOUTP: C36.1, JP1.5, L8.2, R16.2
RF_IN: C3.1, CON1.SIG, R1.2
V+_HV: C38.1, IC5.1 (IN), IC5.4 (IN), JP2.3
V-_HV: JP2.4
VCC_HFAMP: C41.1, C44.1, FB3.2, R2.2
VCC_MIX: C40.1, C43.1, C47.1, C51.1, FB2.2, IC3.1 (VCC1), IC3.4 (VCC2), IC3.5 (VCC3), IC3.6 (VCC4), IC3.17 (VCC5), IC3.18 (VCC6), IC3.19 (VCC7)
VIN_PLL: C39.1, C42.1, C46.1, FB1.2, IC2.9 (VIN_LDO_VCO), IC2.18 (VIN_LDO_REF), IC2.28 (VIN_LDO_RF_DIG), IC2.36 (VIN_LDO_4V5)
VREG_4V5: C1.1, C2.1, C4.1, C5.1, C6.2, IC2.2 (VREG_4V5), IC2.3 (VCC_VCO_CORE), IC2.16 (VCC_CPOUT), IC2.32 (VCC_RFOUT)
VREG_DIG: C18.2, C20.2, IC2.26 (VDD_DSM_NDIV), IC2.27 (VREG_DIG)
VREG_REF: C16.1, C19.1, IC2.17 (VDD_PFD), IC2.19 (VREG_REF)
VREG_RF: C14.1, C15.1, IC2.29 (VREG_RF)
VREG_VCO: C7.2, C8.1, C9.1, IC2.8 (VREG_VCO), IC2.14 (VDD_CP)
